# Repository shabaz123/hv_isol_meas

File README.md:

High Voltage Isolated Measurement Board
===========================================

Introduction
------------
This repository contains hardware files for constructing an isolated high voltage interface board, that output 4mV per volt, allowing measurements up to the kilovolt range (the range can be modified by changing some resistor values).

Specifications (currently untested)
-----------------------------------

HV Input: Up to +-550V (1100V p-p in bipolar mode) or 0-1200V (unipolar mode). The mode is set using two resistors (see the notes in the circuit diagram)

Input Load: 1uA

Frequency Response: DC to 125 kHz

Output: 4mV per Volt

Power Source: 5V DC

Circuit Diagram
---------------
[Click here for PDF schematic](https://github.com/shabaz123/hv_isol_meas/blob/main/hv-isol-meas-schematic-rev1.pdf)

Bill of Materials
-----------------

[Click here for PDF BoM](https://github.com/shabaz123/hv_isol_meas/blob/main/hv-isol-meas-bom-rev1.pdf)

The order codes in the last column are Farnell order codes.

| Item | Qty | Reference(s)                           | Value          | Description                                                    | MPN                    | Order Code           |
|------|-----|----------------------------------------|----------------|----------------------------------------------------------------|------------------------|----------------------|
| 1    | 10   | C1, C2, C3, C5, C6, C13, C16, C17, C18, C20 | 1u             | Cap 0805                                                       | GENERIC                | 3369302              |
| 2    | 4   | C4, C9, C14, C15                       | 10u            | Cap 1206                                                       | GENERIC                | 2113073              |
| 3    | 2   | C7, C8                                 | 10p            | Cap 0805 NP0                                                   | GENERIC                | 3369276              |
| 4    | 3   | C10, C11, C12                          | 47u            | Cap Elec 6.3mm dia                                             | GENERIC                | 1144626              |
| 5    | 1   | C19                                    | 100n           | Cap 0805                                                       | GENERIC                | 4061699              |
| 6    | 1   | D3                                     | LED            | LED 1210 Example: ASMT-BG20-AS000                              | ASMT-BG20-AS000        | 1603886              |
| 7    | 1   | J1                                     | SMA Conn       | SMA Right Angle e.g. Molex 73391-0080                          | GENERIC                | 2579835              |
| 8    | 1   | J2                                     | 2-way Pin Hdr  | 2.54mm Pin Header 2-way                                        | GENERIC                | N/A                  |
| 9    | 1   | J3                                     | DC Socket      | DC Socket 5.5+2.1mm, DC10A                                     | FC68148                | 224959               |
| 10   | 3   | L1, L2, L3                             | 2mH            | CM Choke 9.2x6mm Example: SRF0905A-202Y                        | SRF0905A-202Y          | 4203907              |
| 11   | 2   | L4, L5                                 | 200uH          | CM Choke 1210 Example: DLW32MH201XK2L                          | DLW32MH201XK2L         | 2913625              |
| 12   | 1   | OPTO1                                  | HCNR200-300E   | Linear Optocoupler SMD                                         | HCNR200-300E           | 8549710              |
| 13   | 2   | R1, R4                                 | 47k            | Res 0805                                                       | GENERIC                | 9237836              |
| 14   | 1   | R3                                     | 300R           | Res 0805                                                       | GENERIC                | 4177753              |
| 15   | 3   | R5, R8, R13                            | 1k             | Res 0805                                                       | GENERIC                | 1469847              |
| 16   | 1   | R6                                     | 100k           | Res 0805                                                       | GENERIC                | 1469860              |
| 17   | 1   | R11                                    | 39k            | Res 0805                                                       | GENERIC                | 1576482              |
| 18   | 2   | R14, R15                               | 82k            | Res 0805                                                       | GENERIC                | 2447729              |
| 19   | 2   | R7, R17                                | 0R             | Res 2512 0-ohm Example: RC2512JK-070RL                         | RC2512JK-070RL         | 9235825              |
| 20   | 2   | R10, R12                               | 500M           | Res 2512 Vishay CRHP2512AF500MFKE1                             | CRHP2512AF500MFKE1     | 3357767              |
| 21   | 1   | U1                                     | OPA2197DGK     | OpAmp Dual, VSSOP (DGK) package                                | OPA2192 or OPA2197 DGK | OPA2197 is   3117396 |
| 22   | 2   | U2, U5                                 | MCP1541T       | Voltage Ref 4.096V SOT23                                       | MCP1541T-I/TT          | 1084310              |
| 23   | 1   | U3                                     | OPA197         | OpAmp SOT23-5 OPA197IDBVT                                      | OPA197IDBVT            | 3004840              |
| 24   | 1   | U4                                     | 5V DC-DC Isol. | DC-DC 5Vin, +-5Vout Traco TMA, TBA, TMR 2, XP IAxxxxS, IHxxxxS | TMA 0505D              | 1007514              |
| 25   | 1   | U6                                     | TPS60403       | Voltage Inverter Charge Pump SOT23-5                           | TPS60403DBV            | 3123050              |
| 26   | 1   | R18                                    | 47R            | Res 0805                                                       | GENERIC                | 1653007              |
| 27   | 1   | R2                                     | 0R             | Res 0805 0-ohm                                                 | GENERIC                | 1469846              |
| 28   | 2   | FB1, FB2                               | Ferrite Bead   | Ferrite Bead 0805, example is MMZ2012Y102BT000                 | GENERIC                | 1669727              |

Board Layout
-----------------
Top Side:
Note: Capacitor C20 is missing on the Rev 1.0 board. Refer to the Issues list further below, to see where to solder it.

Underside:

3D Render
---------
Top Side:

Underside:

Enclosure
---------
Optionally, the board can be fitted into the following enclosure:

PCB CAM Files (Gerber Files)
----------------------------
[Click here for Gerber zip file](https://github.com/shabaz123/hv_isol_meas/blob/main/hv-isol-meas-gerbers-rev1.zip) that can be sent to any PCB factory.

KiCad Source Files
------------------
Download the entire repo and the KiCad 7 files will be in the kicad_src subdirectory.

Issues
------
1. C20 (1uF) is missing from the rev 1.0 board. The photo here shows where to solder it. One end of the capacitor is soldered to the choke L5, and the other end needs to be connected to 0V. The easiest way to access 0V is to scratch off some of the solder mask on the copper pour, and then solder the capacitor to it.

2. The linear optocoupler (OPTO1) footprint is too narrow on the rev 1.0 board : ( The only fix is to use small pliers to bend the SMD optocoupler legs inwards instead of outwards, and then push the vertical parts of the legs inwards too.

3. There is a signal (about 72 kHz) on the output connection : ( It is about 40 mV p-p. I think it's coming from the DC-DC converter. No solution currently for the rev 1.0 board, it is still being worked on.
4. There is an offset on the output, my board had 20 mV offset. Although this could be nulled out on the connected equipment, it will be good to provide an on-board trimmer for nulling. This is still to be worked on.

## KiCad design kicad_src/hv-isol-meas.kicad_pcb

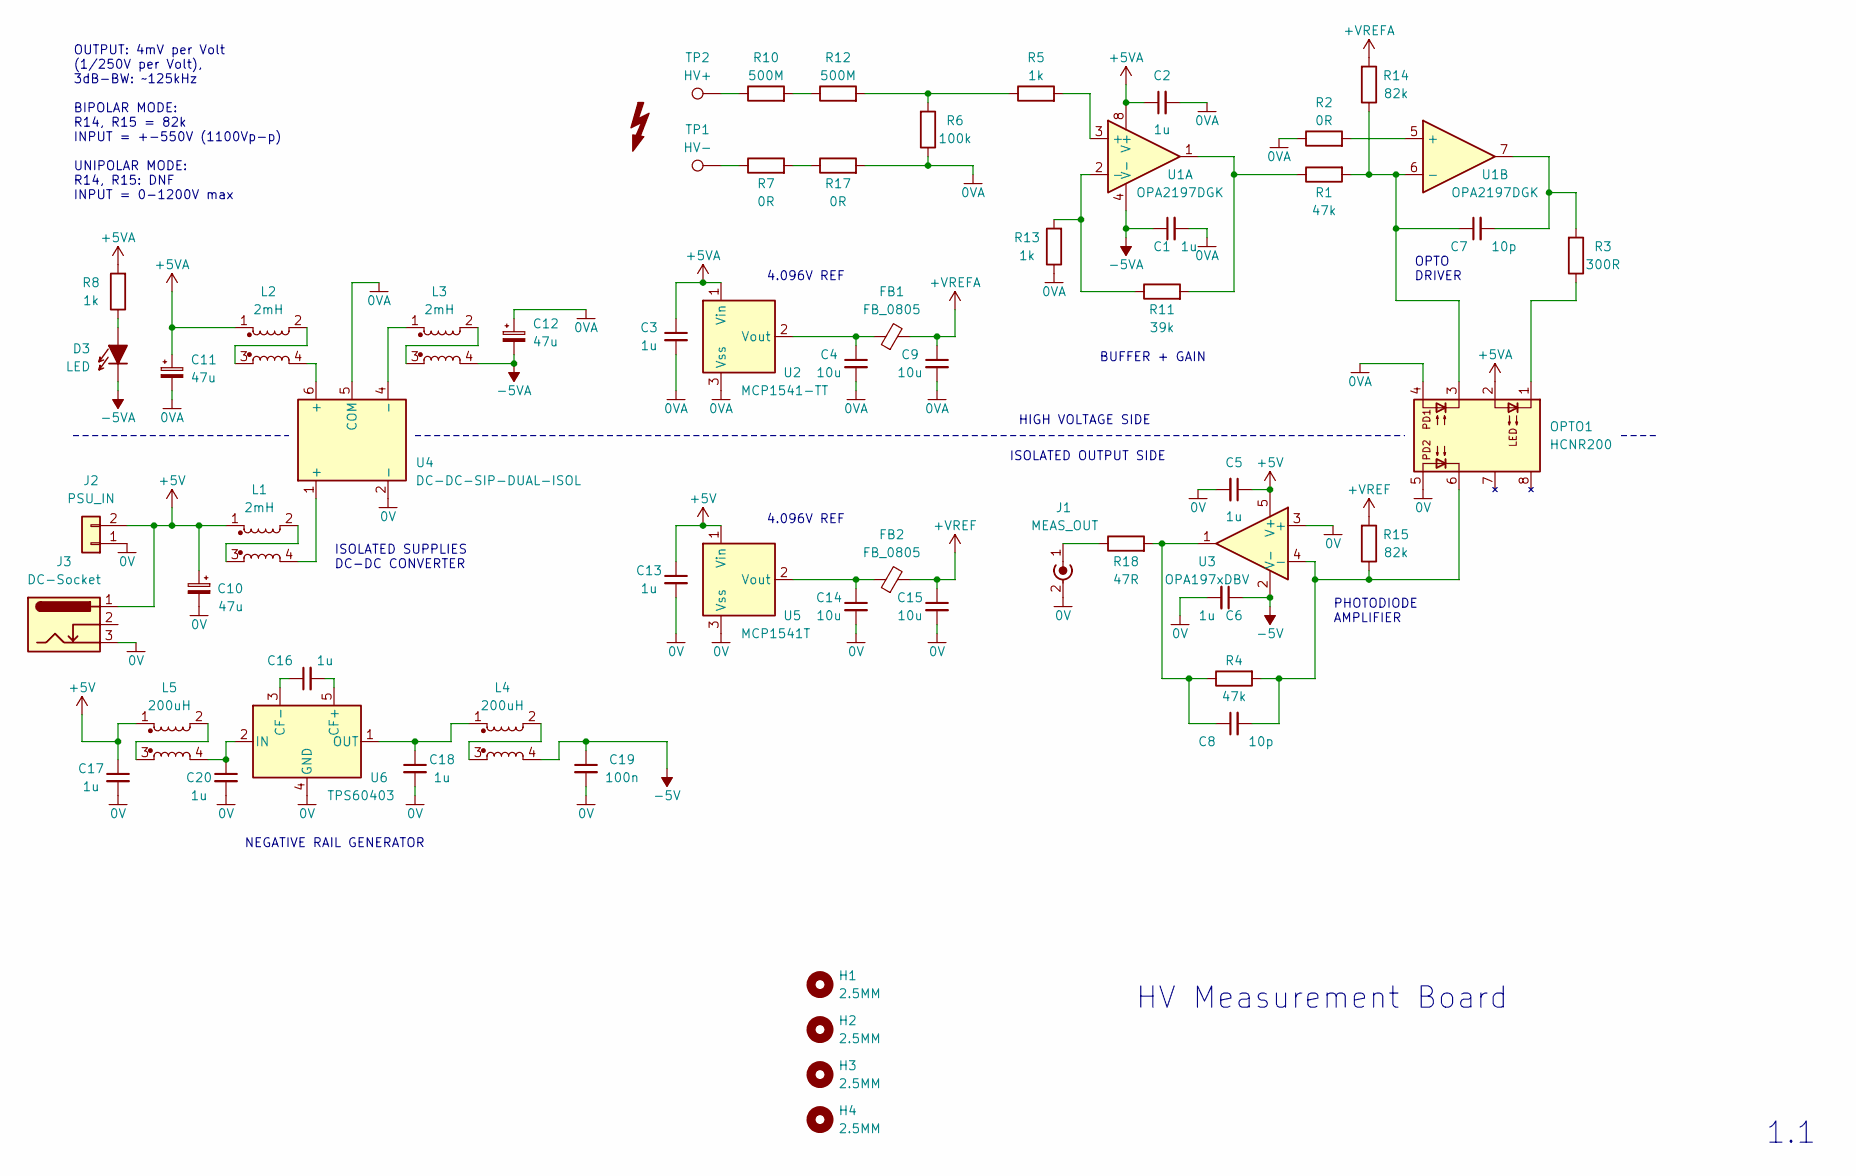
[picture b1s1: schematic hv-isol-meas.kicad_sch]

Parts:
C1, C2, C3, C5, C6, C13, C16, C17, C18, C20: 1u; C_0805_2012Metric_Pad1.18x1.45mm_HandSolder
C4, C9, C14, C15: 10u; C_1206_3216Metric_Pad1.33x1.80mm_HandSolder
C7, C8: 10p; C_0805_2012Metric_Pad1.18x1.45mm_HandSolder
C10, C11, C12: 47u; CP_Radial_D6.3mm_P2.50mm
C19: 100n; C_0805_2012Metric_Pad1.18x1.45mm_HandSolder
D3: LED; LED_1210_3225Metric_Pad1.42x2.65mm_HandSolder
FB1, FB2: FB_0805; R_0805_2012Metric_Pad1.20x1.40mm_HandSolder
H1, H2, H3, H4: 2.5MM; MountingHole_2.5mm
J1: MEAS_OUT; RF-Conn-Vert
J2: PSU_IN; PinHeader_1x02_P2.54mm_Vertical
J3: DC-Socket; DC-Jack-10
L1, L2, L3: 2mH; SRF0905A
L4, L5: 200uH; CHOKE_CM_1210
OPTO1: HCNR200; HCRN200
R1, R4: 47k; R_0805_2012Metric_Pad1.20x1.40mm_HandSolder
R2: 0R; R_0805_2012Metric_Pad1.20x1.40mm_HandSolder
R3: 300R; R_0805_2012Metric_Pad1.20x1.40mm_HandSolder
R5, R8, R13: 1k; R_0805_2012Metric_Pad1.20x1.40mm_HandSolder
R6: 100k; R_0805_2012Metric_Pad1.20x1.40mm_HandSolder
R7, R17: 0R; R_2512_CRHP
R10, R12: 500M; R_2512_CRHP
R11: 39k; R_0805_2012Metric_Pad1.20x1.40mm_HandSolder
R14, R15: 82k; R_0805_2012Metric_Pad1.20x1.40mm_HandSolder
R18: 47R; R_0805_2012Metric_Pad1.20x1.40mm_HandSolder
TP1: HV-; TestPoint_Plated_Hole_1.8mm
TP2: HV+; TestPoint_Plated_Hole_1.8mm
U1: OPA2197DGK; VSSOP-8-DGK-TI
U2: MCP1541-TT; SOT-23-hand-solder
U3: OPA197xDBV; SOT-23-5
U4: DC-DC-SIP-DUAL-ISOL; DCDC-1W
U5: MCP1541T; SOT-23-hand-solder
U6: TPS60403; SOT23-5

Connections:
0V: C5.2, C6.2, C10.2, C13.2, C14.2, C15.2, C17.2, C18.2, C19.2, C20.2, J1.2 (Ext), J2.1, J3.3, OPTO1.5 (GND), U3.3 (+), U4.2 (-), U5.3 (Vss), U6.4 (GND)
0VA: C1.2, C2.2, C3.2, C4.2, C9.2, C11.2, C12.1, OPTO1.4 (A2), R2.1, R6.1, R13.1, R17.2, U2.3 (Vss), U4.5 (COM)
+5V: C5.1, C10.1, C13.1, C17.1, J2.2, J3.1, L1.1, L5.1, U3.5 (V+), U5.1 (Vin)
+5VA: C2.1, C3.1, C11.1, L2.1, OPTO1.2 (C1), R8.2, U1.8 (V+), U2.1 (Vin)
+VREF: C15.1, FB2.2, R15.2
+VREFA: C9.1, FB1.2, R14.2
-5V: C6.1, C19.1, L4.4, U3.2 (V-)
-5VA: C1.1, C12.2, D3.1 (K), L3.4, U1.4 (V-)
unnamed: C7.2, R3.2, U1.7
unnamed: C8.1, R4.1, R18.2, U3.1
unnamed: D3.2 (A), R8.1
unnamed: J1.1 (In), R18.1
unnamed: L1.2, L1.3
unnamed: L1.4, U4.1 (+)
unnamed: L2.2, L2.3
unnamed: L2.4, U4.6 (+)
unnamed: L3.1, U4.4 (-)
unnamed: L3.2, L3.3
unnamed: L4.2, L4.3
unnamed: L5.2, L5.3
unnamed: OPTO1.1 (A1), R3.1
unnamed: C7.1, OPTO1.3 (C2), R1.2, R14.1, U1.6 (-)
unnamed: C8.2, OPTO1.6 (VO2), R4.2, R15.1, U3.4 (-)
unnamed: R1.1, R11.2, U1.1
unnamed: R7.1, TP1.1
unnamed: R10.1, TP2.1
unnamed: R10.2, R12.1
unnamed: R5.1, R6.2, R12.2
unnamed: R7.2, R17.1
unnamed: R5.2, U1.3 (+)
unnamed: R11.1, R13.2, U1.2 (-)
unnamed: R2.2, U1.5 (+)
unnamed: C4.1, FB1.1, U2.2 (Vout)
unnamed: C14.1, FB2.1, U5.2 (Vout)
unnamed: C16.2, U6.5 (CF+)
unnamed: C16.1, U6.3 (CF-)
unnamed: C20.1, L5.4, U6.2 (IN)
unnamed: C18.1, L4.1, U6.1 (OUT)

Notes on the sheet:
4.096V REF
HIGH VOLTAGE SIDE
ISOLATED OUTPUT SIDE
OPTO DRIVER
ISOLATED SUPPLIES DC-DC CONVERTER
BUFFER + GAIN
NEGATIVE RAIL GENERATOR
1.1
PHOTODIODE AMPLIFIER
OUTPUT: 4mV per Volt (1/250V per Volt), 3dB-BW: ~125kHz BIPOLAR MODE: R14, R15 = 82k INPUT = +-550V (1100Vp-p) UNIPOLAR MODE: R14, R15: DNF INPUT = 0-1200V max
HV Measurement Board

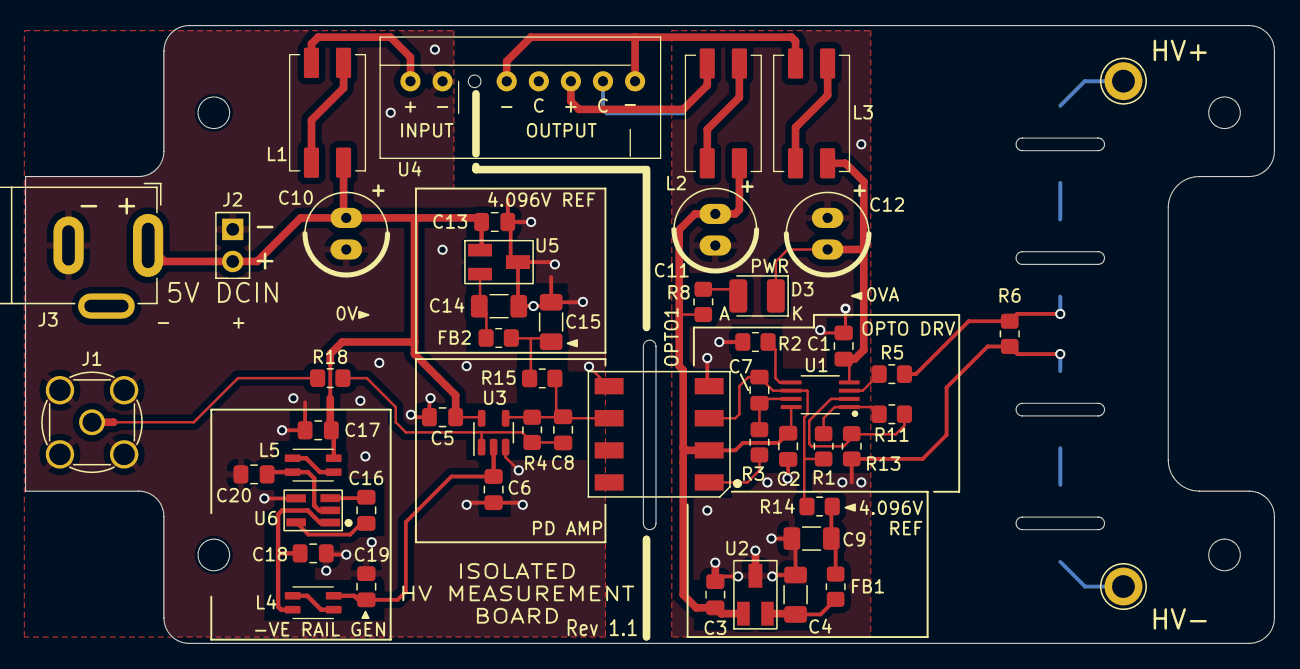
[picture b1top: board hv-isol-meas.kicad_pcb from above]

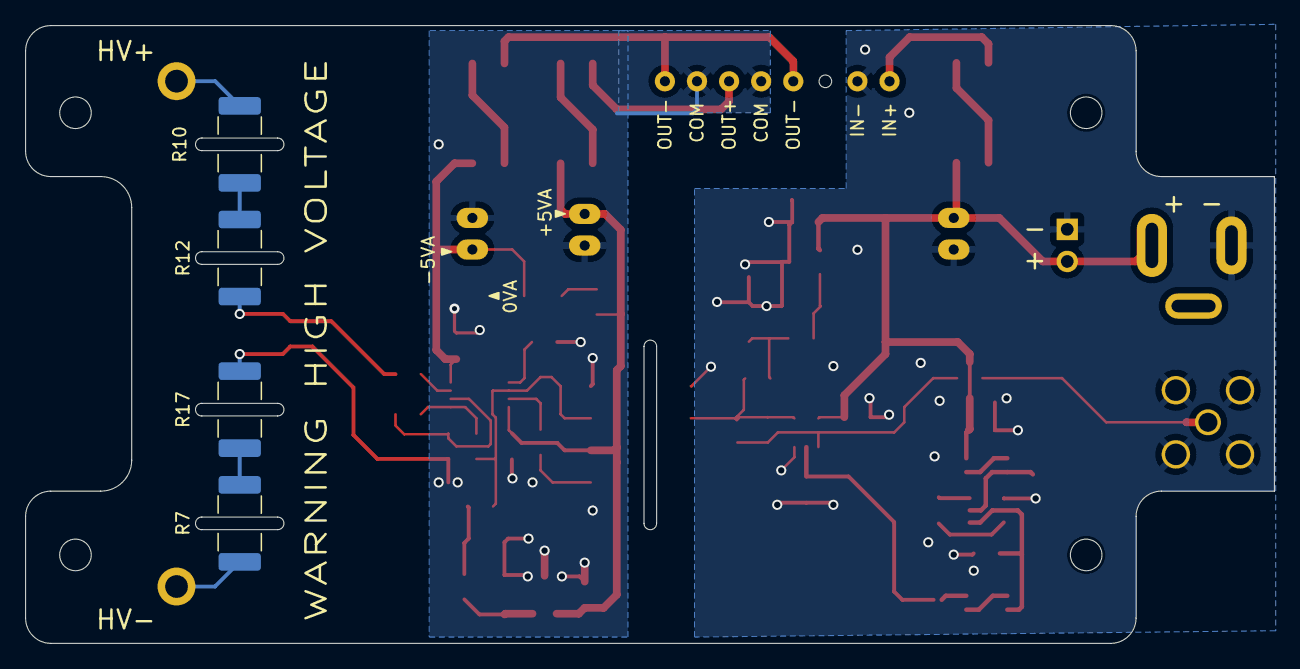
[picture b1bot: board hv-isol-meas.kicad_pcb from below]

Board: 2 copper layers, 98.8 x 48.9 mm, 60 parts (4 on the bottom side), 38 nets.

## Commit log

2023-12-12 Added R18 and C20 to BoM
